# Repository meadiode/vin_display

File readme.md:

# Vintage display module

A series of RP2040 based display modules for 3d-printers using dot-matrix, or 16-segment vintage display ICs.
Intended to be used with [Klipper firmware](https://www.klipper3d.org/).

Currently the following displays were built and tested:

## VinDisplay mdl2416c_x10
Display module features ten MDL2416C which are 4-character 16-segment LED displays.

## VinDisplay hdsp2112_x6
Display module features six HDSP-2112 which are 8-character 5x7 LED dot-matrix displays.

## DemoBoard 1
Simplistic demo-board to evaluate MDL2416C(16-segment LED display), 8 of them are driven by a pico_w. The board just displays current time and date and also prints custom message through a web-interface.

## Building Firmware

### Prerequisites 

Generally, refer to the official [Getting started guide](https://datasheets.raspberrypi.com/pico/getting-started-with-pico.pdf)

You'll need to have:

- ARM embedded gcc toolchain
- GDB (gdb-multiarch)
- Pico SDK
- Pico probe
- FreeRTOS
- Pico OpenOCD

The following environment constants should be defined:
```
PICO_SDK_PATH=/* Path to the root of pico-sdk directory */
FREERTOS_KERNEL_PATH=/* Path to the root of FreeRTOS kernel directory */
```

### Configuring and building

```
cd src
mkdir build
cd build
cmake -DCMAKE_BUILD_TYPE=Debug ..

make
```

### Running and debugging

Connect the picoprobe to the target pico_w board according to the "getting started guide", then run the following:

```
cd [Pico OpenOCD source directory]
sudo src/openocd -f interface/picoprobe.cfg -f target/rp2040.cfg -s tcl
```
It should start a GDB server on the default port 3333.

To flash and run/debug the firmware navigate to the project's directory and run the following: 
```
cd build
gdb-multiarch ./<binary name>.elf
```
Once GDB started:
```
target remote :3333
load
monitor init reset
cont
```

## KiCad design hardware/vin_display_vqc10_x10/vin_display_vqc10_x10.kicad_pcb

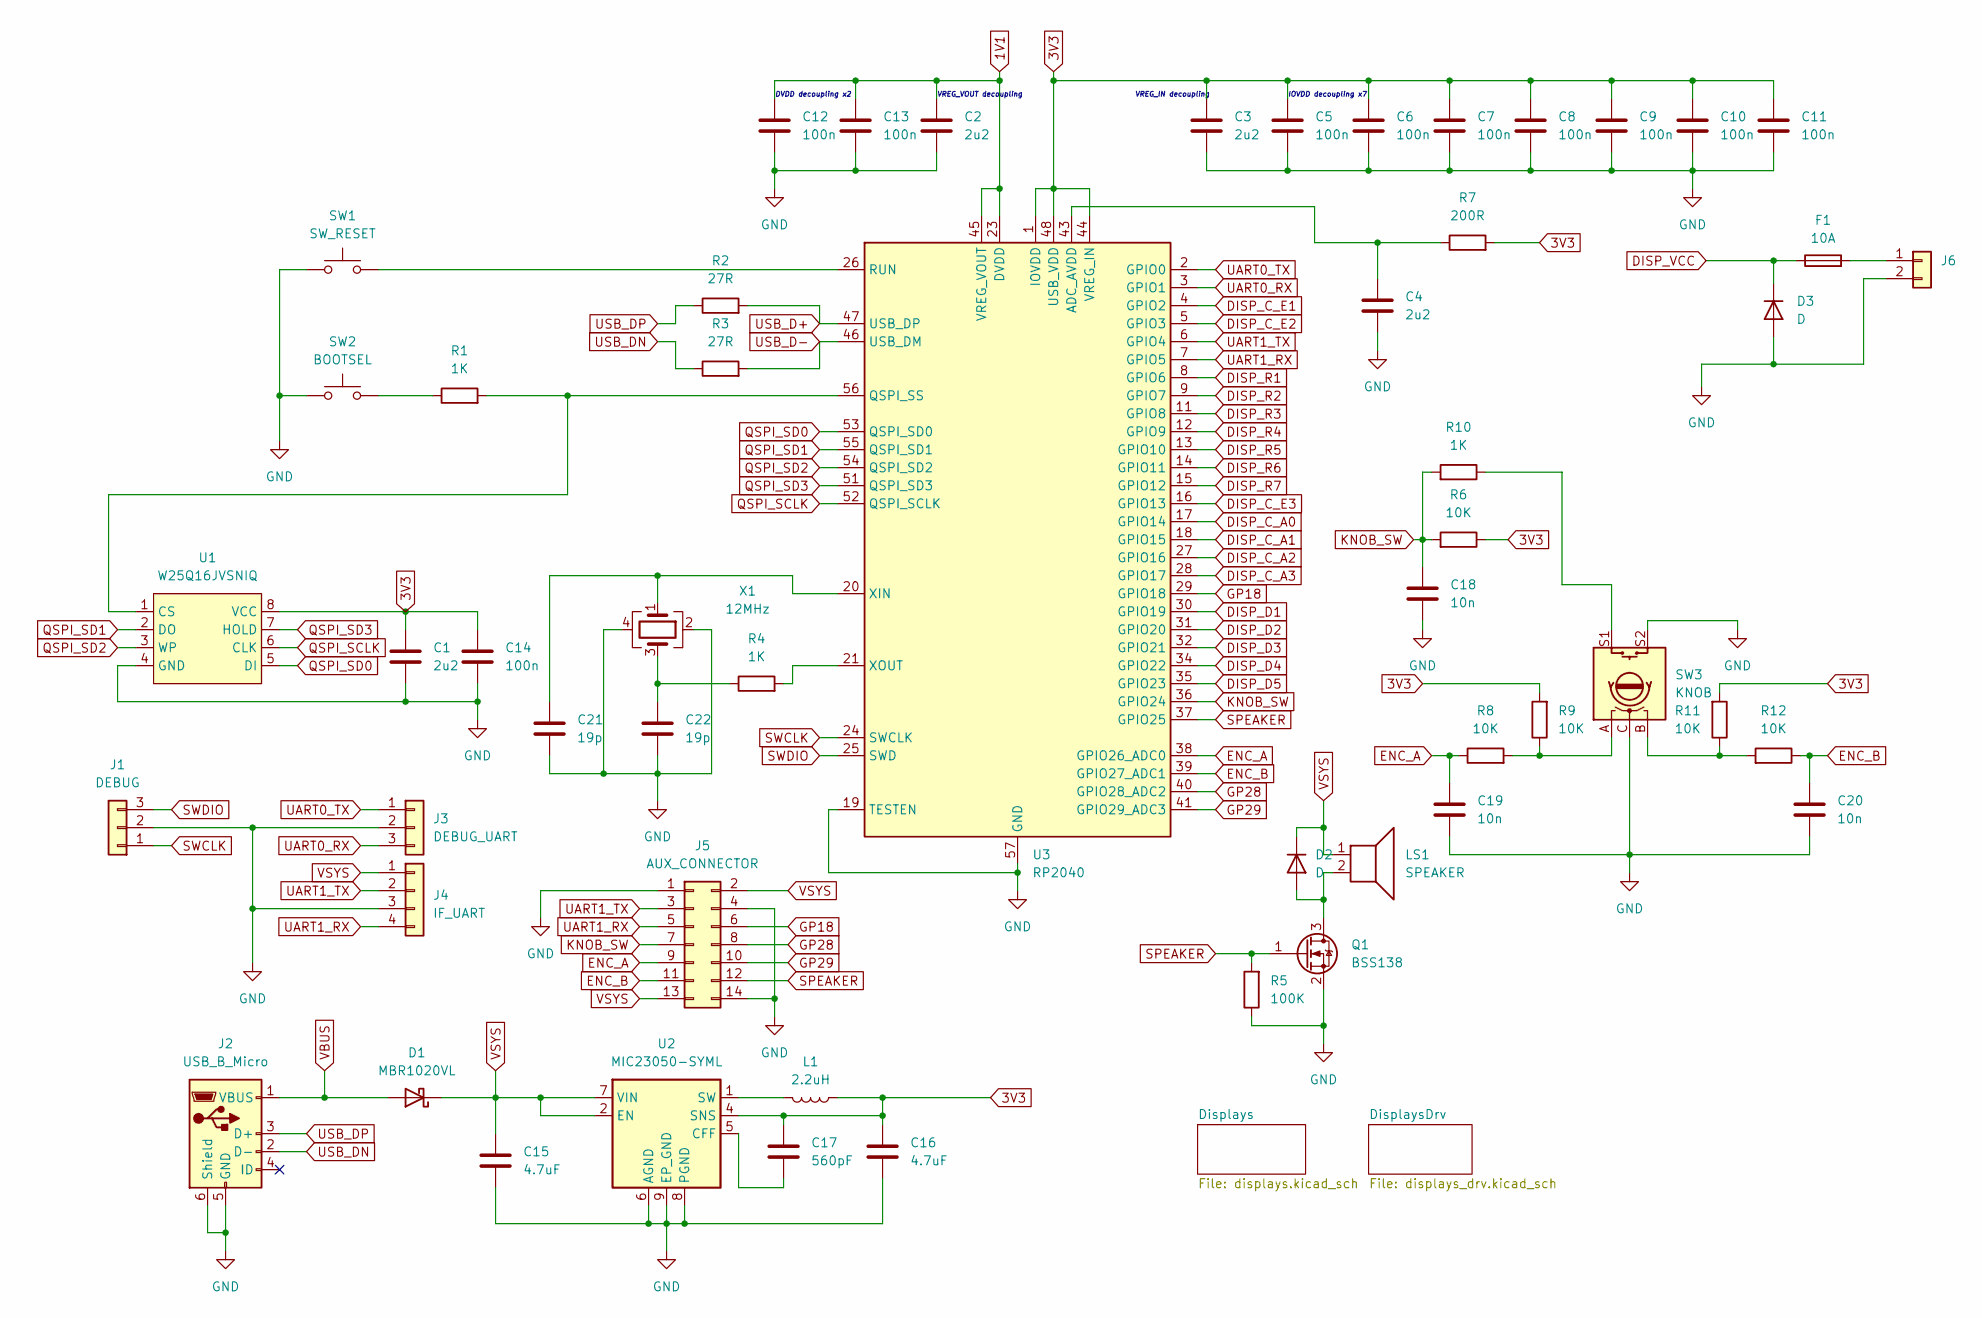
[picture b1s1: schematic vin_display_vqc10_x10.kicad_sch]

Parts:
C1, C2, C3, C4: 2u2; C_0603_1608Metric
C5, C6, C7, C8, C9, C10, C11, C12, C13, C14: 100n; C_0603_1608Metric
C15, C16: 4.7uF; C_0603_1608Metric
C17: 560pF; C_0603_1608Metric
C18, C19, C20: 10n; C_0603_1608Metric
C21, C22: 19p; C_0603_1608Metric
D1: MBR1020VL; D_SOD-123F
D2: D; D_SOD-123
D3: D; Diode_TO252
F1: 10A; Fuse_2410
J1: DEBUG; JST_EH_B3B-EH-A_1x03_P2.50mm_Vertical
J2: USB_B_Micro; GCT_USB3140
J3: DEBUG_UART; JST_EH_B3B-EH-A_1x03_P2.50mm_Vertical
J4: IF_UART; JST_EH_B4B-EH-A_1x04_P2.50mm_Vertical
J5: AUX_CONNECTOR; IDC-Header_2x07_P2.54mm_Vertical
J6: Conn_01x02; Conn_2x3_96
L1: 2.2uH; Inductor_0806
LS1: SPEAKER; BUZZER_CMT-8504
Q1: BSS138; SOT-23
R1, R4, R10: 1K; R_0603_1608Metric
R2, R3: 27R; R_0603_1608Metric
R5: 100K; R_0603_1608Metric
R6, R8, R9, R11, R12: 10K; R_0603_1608Metric
R7: 200R; R_0603_1608Metric
SW1: SW_RESET; TS18_TACTILE_SWITCH
SW2: BOOTSEL; TS18_TACTILE_SWITCH
SW3: KNOB; PEC11H_Encoder
U1: W25Q16JVSNIQ; SOIC8_150mil
U2: MIC23050-SYML; Micrel_MLF-8-1EP_2x2mm_P0.5mm_EP0.6x1.2mm
U3: RP2040; QFN-56-1EP_7x7mm_P0.4mm_EP3.2x3.2mm
X1: 12MHz; Crystal_SMD_Abracon_ABM8AIG-4Pin_3.2x2.5mm

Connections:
1V1: C2.1, C12.1, C13.1, U3.23 (DVDD), U3.45 (VREG_VOUT), U3.50 (DVDD)
3V3: C1.1, C3.1, C5.1, C6.1, C7.1, C8.1, C9.1, C10.1, C11.1, C14.1, C16.1, C17.1, L1.1, R6.1, R7.2, R9.2, R11.2, U1.8 (VCC), U2.4 (SNS), U3.1 (IOVDD), U3.10 (IOVDD), U3.22 (IOVDD), U3.33 (IOVDD), U3.42 (IOVDD), U3.44 (VREG_IN), U3.48 (USB_VDD), U3.49 (IOVDD); also elsewhere on the board
DISP_C_A0: U3.17 (GPIO14); also elsewhere on the board
DISP_C_A1: U3.18 (GPIO15); also elsewhere on the board
DISP_C_A2: U3.27 (GPIO16); also elsewhere on the board
DISP_C_A3: U3.28 (GPIO17); also elsewhere on the board
DISP_C_E1: U3.4 (GPIO2); also elsewhere on the board
DISP_C_E2: U3.5 (GPIO3); also elsewhere on the board
DISP_C_E3: U3.16 (GPIO13); also elsewhere on the board
DISP_D1: U3.30 (GPIO19); also elsewhere on the board
DISP_D2: U3.31 (GPIO20); also elsewhere on the board
DISP_D3: U3.32 (GPIO21); also elsewhere on the board
DISP_D4: U3.34 (GPIO22); also elsewhere on the board
DISP_D5: U3.35 (GPIO23); also elsewhere on the board
DISP_R1: U3.8 (GPIO6); also elsewhere on the board
DISP_R2: U3.9 (GPIO7); also elsewhere on the board
DISP_R3: U3.11 (GPIO8); also elsewhere on the board
DISP_R4: U3.12 (GPIO9); also elsewhere on the board
DISP_R5: U3.13 (GPIO10); also elsewhere on the board
DISP_R6: U3.14 (GPIO11); also elsewhere on the board
DISP_R7: U3.15 (GPIO12); also elsewhere on the board
DISP_VCC: D3.1 (K), F1.1; also elsewhere on the board
ENC_A: C19.1, J5.9, R8.1, U3.38 (GPIO26_ADC0)
ENC_B: C20.1, J5.11, R12.1, U3.39 (GPIO27_ADC1)
GND: C1.2, C2.2, C3.2, C4.2, C5.2, C6.2, C7.2, C8.2, C9.2, C10.2, C11.2, C12.2, C13.2, C14.2, C15.2, C16.2, C18.2, C19.2, C20.2, C21.2, C22.2, D3.2 (A), J1.2, J2.5 (GND), J2.6 (Shield), J3.2, J4.3, J5.1, J5.4, J5.14, J6.2, Q1.2 (S), R5.1, SW1.1, SW2.1, SW3.C, SW3.S2, U1.4 (GND), U2.6 (AGND), U2.8 (PGND), U2.9 (EP_GND), U3.19 (TESTEN), U3.57 (GND), X1.2, X1.4; also elsewhere on the board
GP18: J5.6, U3.29 (GPIO18)
GP28: J5.8, U3.40 (GPIO28_ADC2)
GP29: J5.10, U3.41 (GPIO29_ADC3)
KNOB_SW: C18.1, J5.7, R6.2, R10.2, U3.36 (GPIO24)
unnamed: C22.1, R4.1, X1.3
unnamed: D2.2 (A), LS1.2, Q1.3 (D)
unnamed: F1.2, J6.1
unnamed: R1.1, SW2.2
unnamed: R8.2, R9.1, SW3.A
unnamed: R10.1, SW3.S1
unnamed: R11.1, R12.2, SW3.B
unnamed: R1.2, U1.1 (CS), U3.56 (QSPI_SS)
unnamed: C17.2, U2.5 (CFF)
unnamed: L1.2, U2.1 (SW)
unnamed: C4.1, R7.1, U3.43 (ADC_AVDD)
unnamed: SW1.2, U3.26 (RUN)
unnamed: C21.1, U3.20 (XIN), X1.1
unnamed: R4.2, U3.21 (XOUT)
QSPI_SCLK: U1.6 (CLK), U3.52 (QSPI_SCLK)
QSPI_SD0: U1.5 (DI), U3.53 (QSPI_SD0)
QSPI_SD1: U1.2 (DO), U3.55 (QSPI_SD1)
QSPI_SD2: U1.3 (WP), U3.54 (QSPI_SD2)
QSPI_SD3: U1.7 (HOLD), U3.51 (QSPI_SD3)
SPEAKER: J5.12, Q1.1 (G), R5.2, U3.37 (GPIO25)
SWCLK: J1.1, U3.24 (SWCLK)
SWDIO: J1.3, U3.25 (SWD)
UART0_RX: J3.3, U3.3 (GPIO1)
UART0_TX: J3.1, U3.2 (GPIO0)
UART1_RX: J4.4, J5.5, U3.7 (GPIO5)
UART1_TX: J4.2, J5.3, U3.6 (GPIO4)
USB_D+: R2.2, U3.47 (USB_DP)
USB_D-: R3.2, U3.46 (USB_DM)
USB_DN: J2.2 (D-), R3.1
USB_DP: J2.3 (D+), R2.1
VBUS: D1.2 (A), J2.1 (VBUS)
VSYS: C15.1, D1.1 (K), D2.1 (K), J4.1, J5.2, J5.13, LS1.1, U2.2 (EN), U2.7 (VIN)

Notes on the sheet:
IOVDD decoupling x7
DVDD decoupling x2
VREG_IN decoupling
VREG_VOUT decoupling

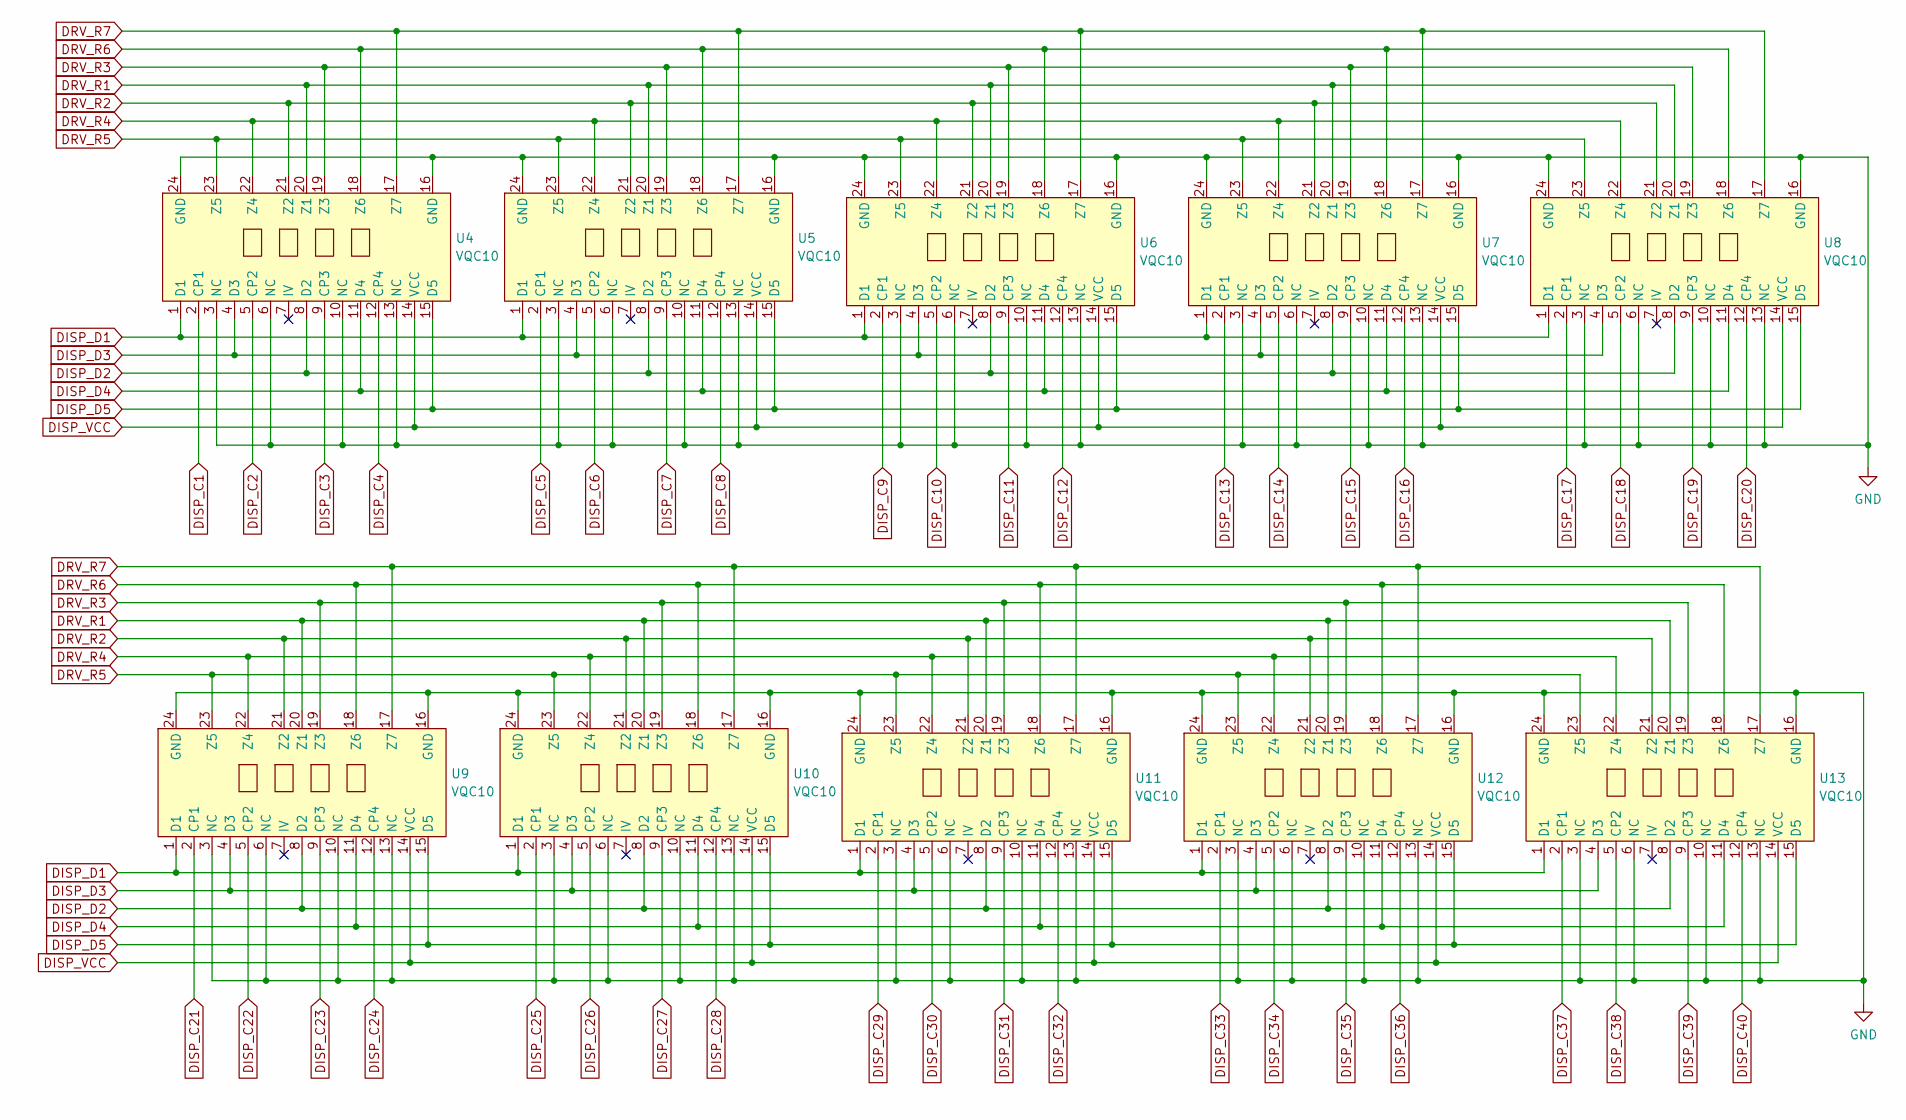
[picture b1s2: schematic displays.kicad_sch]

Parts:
U4, U5, U6, U7, U8, U9, U10, U11, U12, U13: VQC10

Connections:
DISP_C1: U4.2 (CP1); also elsewhere on the board
DISP_C2: U4.5 (CP2); also elsewhere on the board
DISP_C3: U4.9 (CP3); also elsewhere on the board
DISP_C4: U4.12 (CP4); also elsewhere on the board
DISP_C5: U5.2 (CP1); also elsewhere on the board
DISP_C6: U5.5 (CP2); also elsewhere on the board
DISP_C7: U5.9 (CP3); also elsewhere on the board
DISP_C8: U5.12 (CP4); also elsewhere on the board
DISP_C9: U6.2 (CP1); also elsewhere on the board
DISP_C10: U6.5 (CP2); also elsewhere on the board
DISP_C11: U6.9 (CP3); also elsewhere on the board
DISP_C12: U6.12 (CP4); also elsewhere on the board
DISP_C13: U7.2 (CP1); also elsewhere on the board
DISP_C14: U7.5 (CP2); also elsewhere on the board
DISP_C15: U7.9 (CP3); also elsewhere on the board
DISP_C16: U7.12 (CP4); also elsewhere on the board
DISP_C17: U8.2 (CP1); also elsewhere on the board
DISP_C18: U8.5 (CP2); also elsewhere on the board
DISP_C19: U8.9 (CP3); also elsewhere on the board
DISP_C20: U8.12 (CP4); also elsewhere on the board
DISP_C21: U9.2 (CP1); also elsewhere on the board
DISP_C22: U9.5 (CP2); also elsewhere on the board
DISP_C23: U9.9 (CP3); also elsewhere on the board
DISP_C24: U9.12 (CP4); also elsewhere on the board
DISP_C25: U10.2 (CP1); also elsewhere on the board
DISP_C26: U10.5 (CP2); also elsewhere on the board
DISP_C27: U10.9 (CP3); also elsewhere on the board
DISP_C28: U10.12 (CP4); also elsewhere on the board
DISP_C29: U11.2 (CP1); also elsewhere on the board
DISP_C30: U11.5 (CP2); also elsewhere on the board
DISP_C31: U11.9 (CP3); also elsewhere on the board
DISP_C32: U11.12 (CP4); also elsewhere on the board
DISP_C33: U12.2 (CP1); also elsewhere on the board
DISP_C34: U12.5 (CP2); also elsewhere on the board
DISP_C35: U12.9 (CP3); also elsewhere on the board
DISP_C36: U12.12 (CP4); also elsewhere on the board
DISP_C37: U13.2 (CP1); also elsewhere on the board
DISP_C38: U13.5 (CP2); also elsewhere on the board
DISP_C39: U13.9 (CP3); also elsewhere on the board
DISP_C40: U13.12 (CP4); also elsewhere on the board
DISP_D1: U4.1 (D1), U5.1 (D1), U6.1 (D1), U7.1 (D1), U8.1 (D1), U9.1 (D1), U10.1 (D1), U11.1 (D1), U12.1 (D1), U13.1 (D1); also elsewhere on the board
DISP_D2: U4.8 (D2), U5.8 (D2), U6.8 (D2), U7.8 (D2), U8.8 (D2), U9.8 (D2), U10.8 (D2), U11.8 (D2), U12.8 (D2), U13.8 (D2); also elsewhere on the board
DISP_D3: U4.4 (D3), U5.4 (D3), U6.4 (D3), U7.4 (D3), U8.4 (D3), U9.4 (D3), U10.4 (D3), U11.4 (D3), U12.4 (D3), U13.4 (D3); also elsewhere on the board
DISP_D4: U4.11 (D4), U5.11 (D4), U6.11 (D4), U7.11 (D4), U8.11 (D4), U9.11 (D4), U10.11 (D4), U11.11 (D4), U12.11 (D4), U13.11 (D4); also elsewhere on the board
DISP_D5: U4.15 (D5), U5.15 (D5), U6.15 (D5), U7.15 (D5), U8.15 (D5), U9.15 (D5), U10.15 (D5), U11.15 (D5), U12.15 (D5), U13.15 (D5); also elsewhere on the board
DISP_VCC: U4.14 (VCC), U5.14 (VCC), U6.14 (VCC), U7.14 (VCC), U8.14 (VCC), U9.14 (VCC), U10.14 (VCC), U11.14 (VCC), U12.14 (VCC), U13.14 (VCC); also elsewhere on the board
DRV_R1: U4.20 (Z1), U5.20 (Z1), U6.20 (Z1), U7.20 (Z1), U8.20 (Z1), U9.20 (Z1), U10.20 (Z1), U11.20 (Z1), U12.20 (Z1), U13.20 (Z1); also elsewhere on the board
DRV_R2: U4.21 (Z2), U5.21 (Z2), U6.21 (Z2), U7.21 (Z2), U8.21 (Z2), U9.21 (Z2), U10.21 (Z2), U11.21 (Z2), U12.21 (Z2), U13.21 (Z2); also elsewhere on the board
DRV_R3: U4.19 (Z3), U5.19 (Z3), U6.19 (Z3), U7.19 (Z3), U8.19 (Z3), U9.19 (Z3), U10.19 (Z3), U11.19 (Z3), U12.19 (Z3), U13.19 (Z3); also elsewhere on the board
DRV_R4: U4.22 (Z4), U5.22 (Z4), U6.22 (Z4), U7.22 (Z4), U8.22 (Z4), U9.22 (Z4), U10.22 (Z4), U11.22 (Z4), U12.22 (Z4), U13.22 (Z4); also elsewhere on the board
DRV_R5: U4.23 (Z5), U5.23 (Z5), U6.23 (Z5), U7.23 (Z5), U8.23 (Z5), U9.23 (Z5), U10.23 (Z5), U11.23 (Z5), U12.23 (Z5), U13.23 (Z5); also elsewhere on the board
DRV_R6: U4.18 (Z6), U5.18 (Z6), U6.18 (Z6), U7.18 (Z6), U8.18 (Z6), U9.18 (Z6), U10.18 (Z6), U11.18 (Z6), U12.18 (Z6), U13.18 (Z6); also elsewhere on the board
DRV_R7: U4.17 (Z7), U5.17 (Z7), U6.17 (Z7), U7.17 (Z7), U8.17 (Z7), U9.17 (Z7), U10.17 (Z7), U11.17 (Z7), U12.17 (Z7), U13.17 (Z7); also elsewhere on the board
GND: U4.3 (NC), U4.6 (NC), U4.10 (NC), U4.13 (NC), U4.16 (GND), U4.24 (GND), U5.3 (NC), U5.6 (NC), U5.10 (NC), U5.13 (NC), U5.16 (GND), U5.24 (GND), U6.3 (NC), U6.6 (NC), U6.10 (NC), U6.13 (NC), U6.16 (GND), U6.24 (GND), U7.3 (NC), U7.6 (NC), U7.10 (NC), U7.13 (NC), U7.16 (GND), U7.24 (GND), U8.3 (NC), U8.6 (NC), U8.10 (NC), U8.13 (NC), U8.16 (GND), U8.24 (GND), U9.3 (NC), U9.6 (NC), U9.10 (NC), U9.13 (NC), U9.16 (GND), U9.24 (GND), U10.3 (NC), U10.6 (NC), U10.10 (NC), U10.13 (NC), U10.16 (GND), U10.24 (GND), U11.3 (NC), U11.6 (NC), U11.10 (NC), U11.13 (NC), U11.16 (GND), U11.24 (GND), U12.3 (NC), U12.6 (NC), U12.10 (NC), U12.13 (NC), U12.16 (GND), U12.24 (GND), U13.3 (NC), U13.6 (NC), U13.10 (NC), U13.13 (NC), U13.16 (GND), U13.24 (GND); also elsewhere on the board

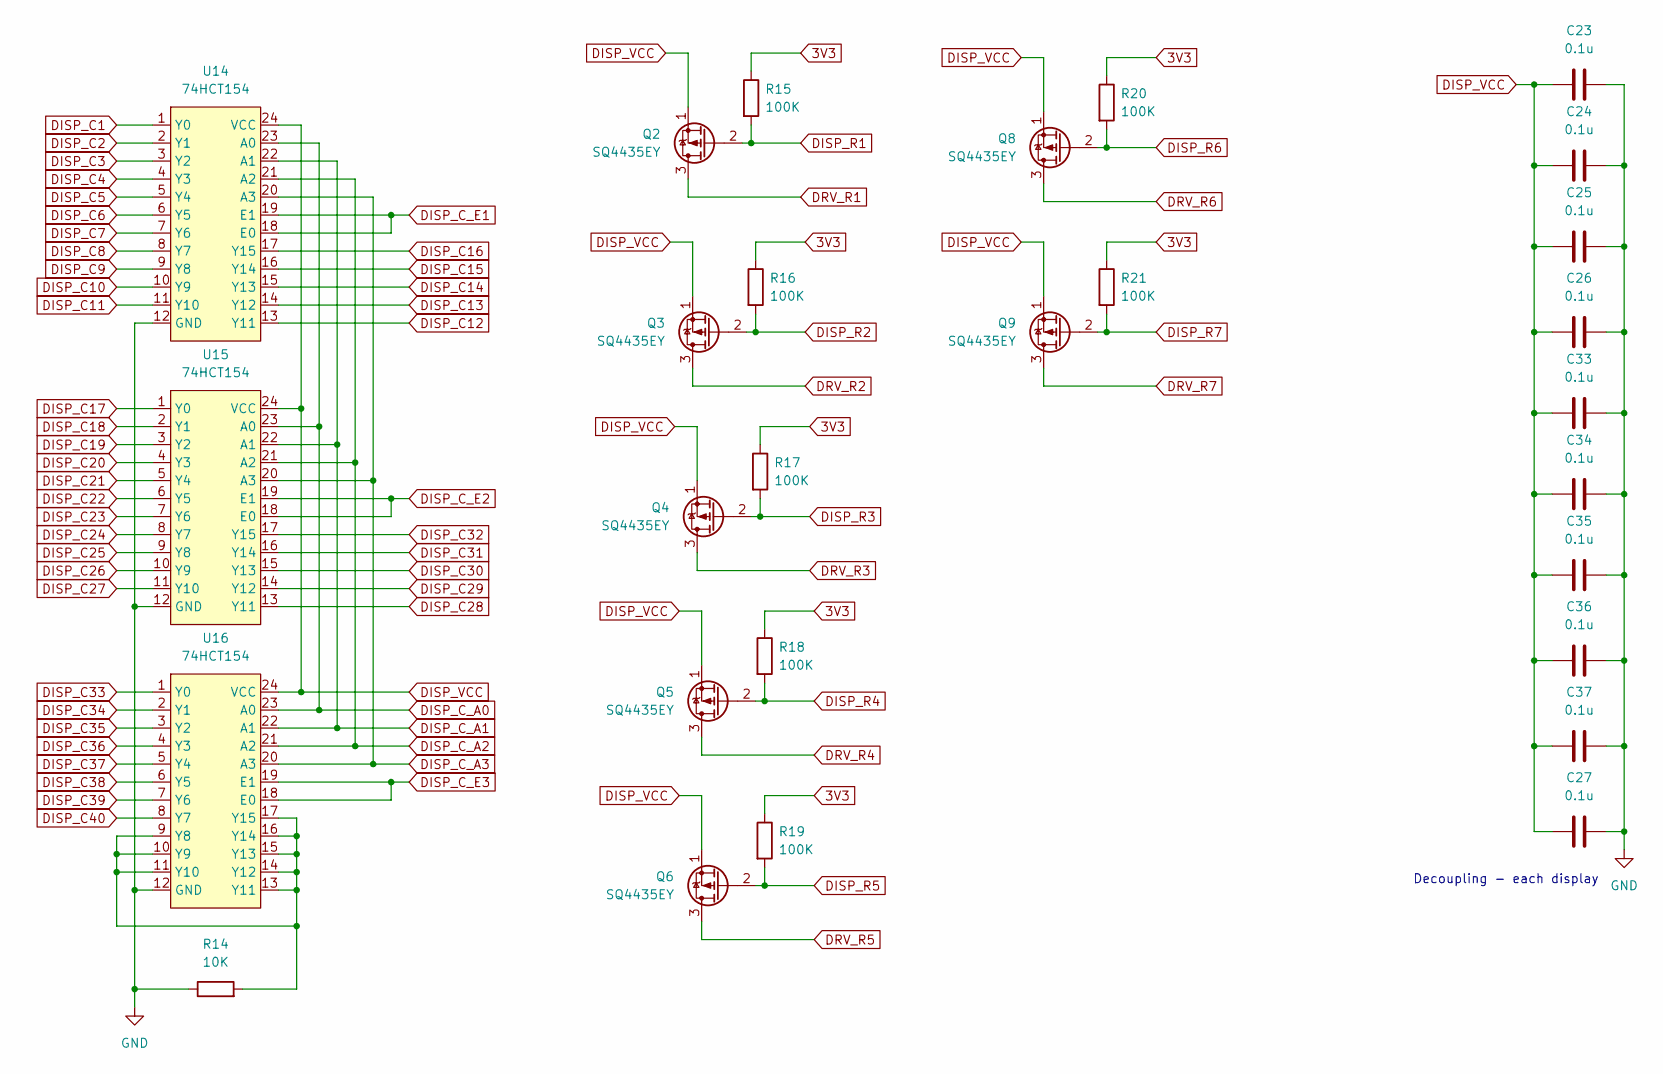
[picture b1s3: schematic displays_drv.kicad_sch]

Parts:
C23, C24, C25, C26, C27, C33, C34, C35, C36, C37: 0.1u; C_0603_1608Metric
Q2, Q3, Q4, Q5, Q6, Q8, Q9: SQ4435EY; SO8_MOSFET_S3G1D4
R14: 10K; C_0603_1608Metric
R15, R16, R17, R18, R19, R20, R21: 100K; R_0603_1608Metric
U14, U15, U16: 74HCT154; TSSOP-24_4.4x7.8mm_P0.65mm

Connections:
3V3: R15.1, R16.1, R17.1, R18.1, R19.1, R20.1, R21.1; also elsewhere on the board
DISP_C1: U14.1 (Y0); also elsewhere on the board
DISP_C2: U14.2 (Y1); also elsewhere on the board
DISP_C3: U14.3 (Y2); also elsewhere on the board
DISP_C4: U14.4 (Y3); also elsewhere on the board
DISP_C5: U14.5 (Y4); also elsewhere on the board
DISP_C6: U14.6 (Y5); also elsewhere on the board
DISP_C7: U14.7 (Y6); also elsewhere on the board
DISP_C8: U14.8 (Y7); also elsewhere on the board
DISP_C9: U14.9 (Y8); also elsewhere on the board
DISP_C10: U14.10 (Y9); also elsewhere on the board
DISP_C11: U14.11 (Y10); also elsewhere on the board
DISP_C12: U14.13 (Y11); also elsewhere on the board
DISP_C13: U14.14 (Y12); also elsewhere on the board
DISP_C14: U14.15 (Y13); also elsewhere on the board
DISP_C15: U14.16 (Y14); also elsewhere on the board
DISP_C16: U14.17 (Y15); also elsewhere on the board
DISP_C17: U15.1 (Y0); also elsewhere on the board
DISP_C18: U15.2 (Y1); also elsewhere on the board
DISP_C19: U15.3 (Y2); also elsewhere on the board
DISP_C20: U15.4 (Y3); also elsewhere on the board
DISP_C21: U15.5 (Y4); also elsewhere on the board
DISP_C22: U15.6 (Y5); also elsewhere on the board
DISP_C23: U15.7 (Y6); also elsewhere on the board
DISP_C24: U15.8 (Y7); also elsewhere on the board
DISP_C25: U15.9 (Y8); also elsewhere on the board
DISP_C26: U15.10 (Y9); also elsewhere on the board
DISP_C27: U15.11 (Y10); also elsewhere on the board
DISP_C28: U15.13 (Y11); also elsewhere on the board
DISP_C29: U15.14 (Y12); also elsewhere on the board
DISP_C30: U15.15 (Y13); also elsewhere on the board
DISP_C31: U15.16 (Y14); also elsewhere on the board
DISP_C32: U15.17 (Y15); also elsewhere on the board
DISP_C33: U16.1 (Y0); also elsewhere on the board
DISP_C34: U16.2 (Y1); also elsewhere on the board
DISP_C35: U16.3 (Y2); also elsewhere on the board
DISP_C36: U16.4 (Y3); also elsewhere on the board
DISP_C37: U16.5 (Y4); also elsewhere on the board
DISP_C38: U16.6 (Y5); also elsewhere on the board
DISP_C39: U16.7 (Y6); also elsewhere on the board
DISP_C40: U16.8 (Y7); also elsewhere on the board
DISP_C_A0: U14.23 (A0), U15.23 (A0), U16.23 (A0); also elsewhere on the board
DISP_C_A1: U14.22 (A1), U15.22 (A1), U16.22 (A1); also elsewhere on the board
DISP_C_A2: U14.21 (A2), U15.21 (A2), U16.21 (A2); also elsewhere on the board
DISP_C_A3: U14.20 (A3), U15.20 (A3), U16.20 (A3); also elsewhere on the board
DISP_C_E1: U14.18 (E0), U14.19 (E1); also elsewhere on the board
DISP_C_E2: U15.18 (E0), U15.19 (E1); also elsewhere on the board
DISP_C_E3: U16.18 (E0), U16.19 (E1); also elsewhere on the board
DISP_R1: Q2.2 (G), R15.2; also elsewhere on the board
DISP_R2: Q3.2 (G), R16.2; also elsewhere on the board
DISP_R3: Q4.2 (G), R17.2; also elsewhere on the board
DISP_R4: Q5.2 (G), R18.2; also elsewhere on the board
DISP_R5: Q6.2 (G), R19.2; also elsewhere on the board
DISP_R6: Q8.2 (G), R20.2; also elsewhere on the board
DISP_R7: Q9.2 (G), R21.2; also elsewhere on the board
DISP_VCC: C23.1, C24.1, C25.1, C26.1, C27.1, C33.1, C34.1, C35.1, C36.1, C37.1, Q2.1 (S), Q3.1 (S), Q4.1 (S), Q5.1 (S), Q6.1 (S), Q8.1 (S), Q9.1 (S), U14.24 (VCC), U15.24 (VCC), U16.24 (VCC); also elsewhere on the board
DRV_R1: Q2.3 (D); also elsewhere on the board
DRV_R2: Q3.3 (D); also elsewhere on the board
DRV_R3: Q4.3 (D); also elsewhere on the board
DRV_R4: Q5.3 (D); also elsewhere on the board
DRV_R5: Q6.3 (D); also elsewhere on the board
DRV_R6: Q8.3 (D); also elsewhere on the board
DRV_R7: Q9.3 (D); also elsewhere on the board
GND: C23.2, C24.2, C25.2, C26.2, C27.2, C33.2, C34.2, C35.2, C36.2, C37.2, R14.1, U14.12 (GND), U15.12 (GND), U16.12 (GND); also elsewhere on the board
unnamed: R14.2, U16.9 (Y8), U16.10 (Y9), U16.11 (Y10), U16.13 (Y11), U16.14 (Y12), U16.15 (Y13), U16.16 (Y14), U16.17 (Y15)

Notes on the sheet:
Decoupling - each display

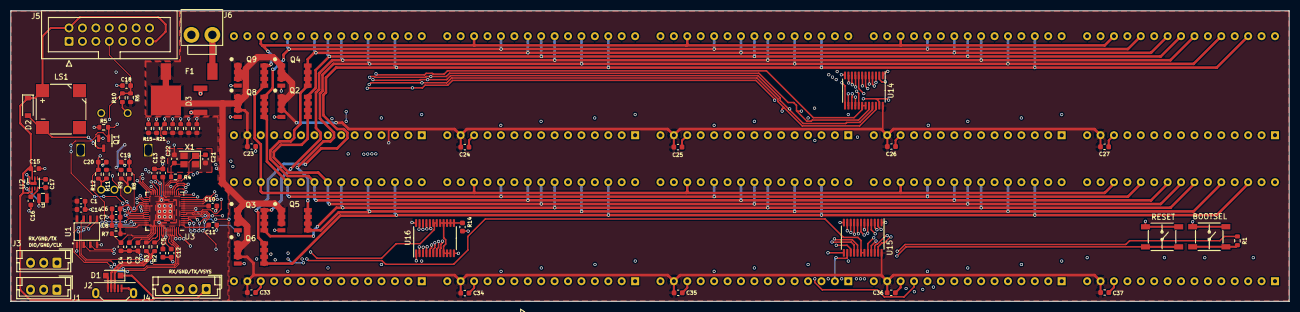
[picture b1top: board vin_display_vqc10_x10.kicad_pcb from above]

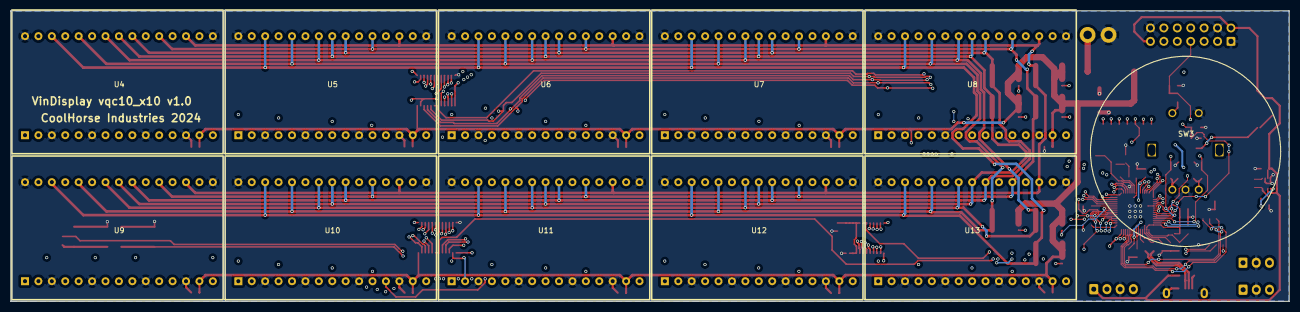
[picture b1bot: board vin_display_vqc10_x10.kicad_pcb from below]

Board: 4 copper layers, 242.0 x 55.0 mm, 92 parts (11 on the bottom side), 109 nets.

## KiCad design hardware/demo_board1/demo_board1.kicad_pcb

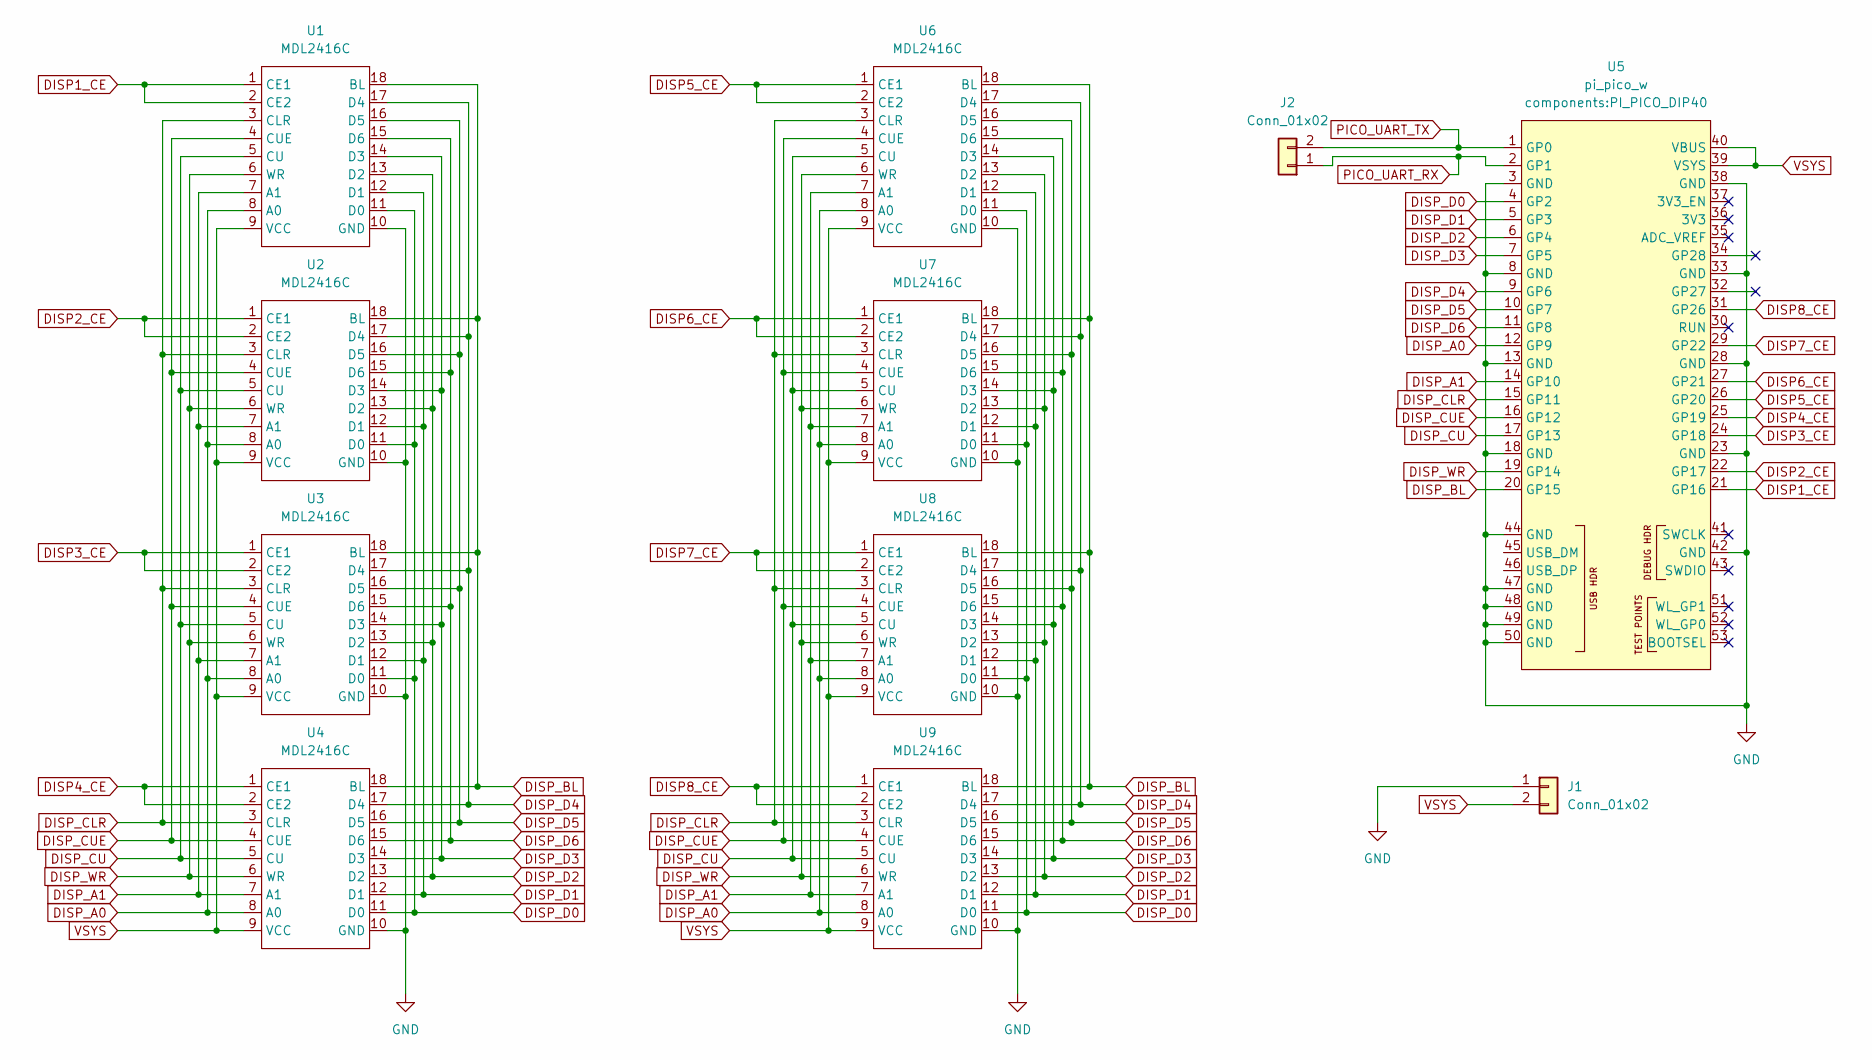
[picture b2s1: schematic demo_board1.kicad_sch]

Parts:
J1, J2: Conn_01x02; PinHeader_1x02_P2.54mm_Vertical
U1, U2, U3, U4, U6, U7, U8, U9: MDL2416C; DIP-18_W60
U5: pi_pico_w; PI_PICO_DIP40

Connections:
DISP1_CE: U1.1 (CE1), U1.2 (CE2), U5.21 (GP16)
DISP2_CE: U2.1 (CE1), U2.2 (CE2), U5.22 (GP17)
DISP3_CE: U3.1 (CE1), U3.2 (CE2), U5.24 (GP18)
DISP4_CE: U4.1 (CE1), U4.2 (CE2), U5.25 (GP19)
DISP5_CE: U5.26 (GP20), U6.1 (CE1), U6.2 (CE2)
DISP6_CE: U5.27 (GP21), U7.1 (CE1), U7.2 (CE2)
DISP7_CE: U5.29 (GP22), U8.1 (CE1), U8.2 (CE2)
DISP8_CE: U5.31 (GP26), U9.1 (CE1), U9.2 (CE2)
DISP_A0: U1.8 (A0), U2.8 (A0), U3.8 (A0), U4.8 (A0), U5.12 (GP9), U6.8 (A0), U7.8 (A0), U8.8 (A0), U9.8 (A0)
DISP_A1: U1.7 (A1), U2.7 (A1), U3.7 (A1), U4.7 (A1), U5.14 (GP10), U6.7 (A1), U7.7 (A1), U8.7 (A1), U9.7 (A1)
DISP_BL: U1.18 (BL), U2.18 (BL), U3.18 (BL), U4.18 (BL), U5.20 (GP15), U6.18 (BL), U7.18 (BL), U8.18 (BL), U9.18 (BL)
DISP_CLR: U1.3 (CLR), U2.3 (CLR), U3.3 (CLR), U4.3 (CLR), U5.15 (GP11), U6.3 (CLR), U7.3 (CLR), U8.3 (CLR), U9.3 (CLR)
DISP_CU: U1.5 (CU), U2.5 (CU), U3.5 (CU), U4.5 (CU), U5.17 (GP13), U6.5 (CU), U7.5 (CU), U8.5 (CU), U9.5 (CU)
DISP_CUE: U1.4 (CUE), U2.4 (CUE), U3.4 (CUE), U4.4 (CUE), U5.16 (GP12), U6.4 (CUE), U7.4 (CUE), U8.4 (CUE), U9.4 (CUE)
DISP_D0: U1.11 (D0), U2.11 (D0), U3.11 (D0), U4.11 (D0), U5.4 (GP2), U6.11 (D0), U7.11 (D0), U8.11 (D0), U9.11 (D0)
DISP_D1: U1.12 (D1), U2.12 (D1), U3.12 (D1), U4.12 (D1), U5.5 (GP3), U6.12 (D1), U7.12 (D1), U8.12 (D1), U9.12 (D1)
DISP_D2: U1.13 (D2), U2.13 (D2), U3.13 (D2), U4.13 (D2), U5.6 (GP4), U6.13 (D2), U7.13 (D2), U8.13 (D2), U9.13 (D2)
DISP_D3: U1.14 (D3), U2.14 (D3), U3.14 (D3), U4.14 (D3), U5.7 (GP5), U6.14 (D3), U7.14 (D3), U8.14 (D3), U9.14 (D3)
DISP_D4: U1.17 (D4), U2.17 (D4), U3.17 (D4), U4.17 (D4), U5.9 (GP6), U6.17 (D4), U7.17 (D4), U8.17 (D4), U9.17 (D4)
DISP_D5: U1.16 (D5), U2.16 (D5), U3.16 (D5), U4.16 (D5), U5.10 (GP7), U6.16 (D5), U7.16 (D5), U8.16 (D5), U9.16 (D5)
DISP_D6: U1.15 (D6), U2.15 (D6), U3.15 (D6), U4.15 (D6), U5.11 (GP8), U6.15 (D6), U7.15 (D6), U8.15 (D6), U9.15 (D6)
DISP_WR: U1.6 (WR), U2.6 (WR), U3.6 (WR), U4.6 (WR), U5.19 (GP14), U6.6 (WR), U7.6 (WR), U8.6 (WR), U9.6 (WR)
GND: J1.1, U1.10 (GND), U2.10 (GND), U3.10 (GND), U4.10 (GND), U5.3 (GND), U5.8 (GND), U5.13 (GND), U5.18 (GND), U5.23 (GND), U5.28 (GND), U5.33 (GND), U5.38 (GND), U5.42 (GND), U5.44 (GND), U5.47 (GND), U5.48 (GND), U5.49 (GND), U5.50 (GND), U6.10 (GND), U7.10 (GND), U8.10 (GND), U9.10 (GND)
PICO_UART_RX: J2.1, U5.2 (GP1)
PICO_UART_TX: J2.2, U5.1 (GP0)
VSYS: J1.2, U1.9 (VCC), U2.9 (VCC), U3.9 (VCC), U4.9 (VCC), U5.39 (VSYS), U5.40 (VBUS), U6.9 (VCC), U7.9 (VCC), U8.9 (VCC), U9.9 (VCC)

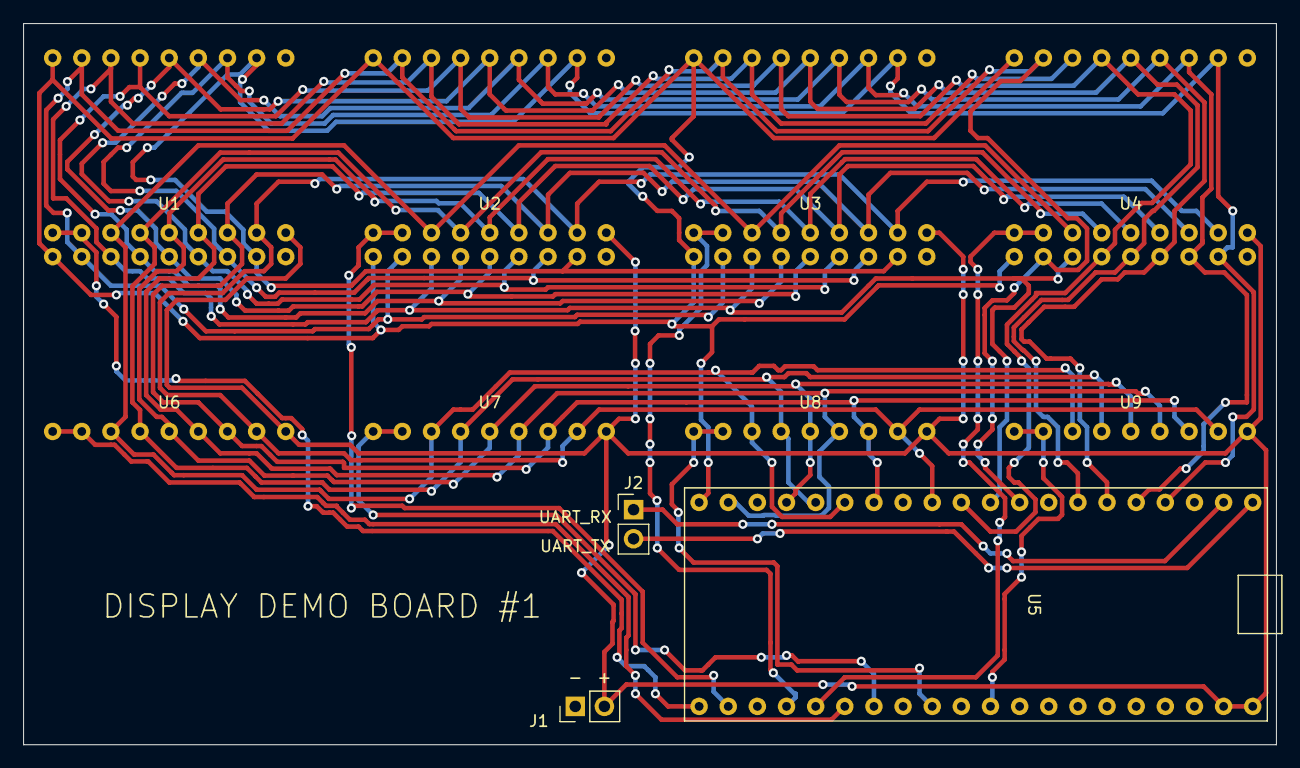
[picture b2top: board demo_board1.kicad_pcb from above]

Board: 2 copper layers, 109.2 x 62.9 mm, 11 parts (0 on the bottom side), 26 nets.

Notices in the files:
hardware/fpanel_remote_pcb_v1/fpanel_remote_pcb.kicad_pcb:
COOLHORSE INDUSTRIES (C) 2022
